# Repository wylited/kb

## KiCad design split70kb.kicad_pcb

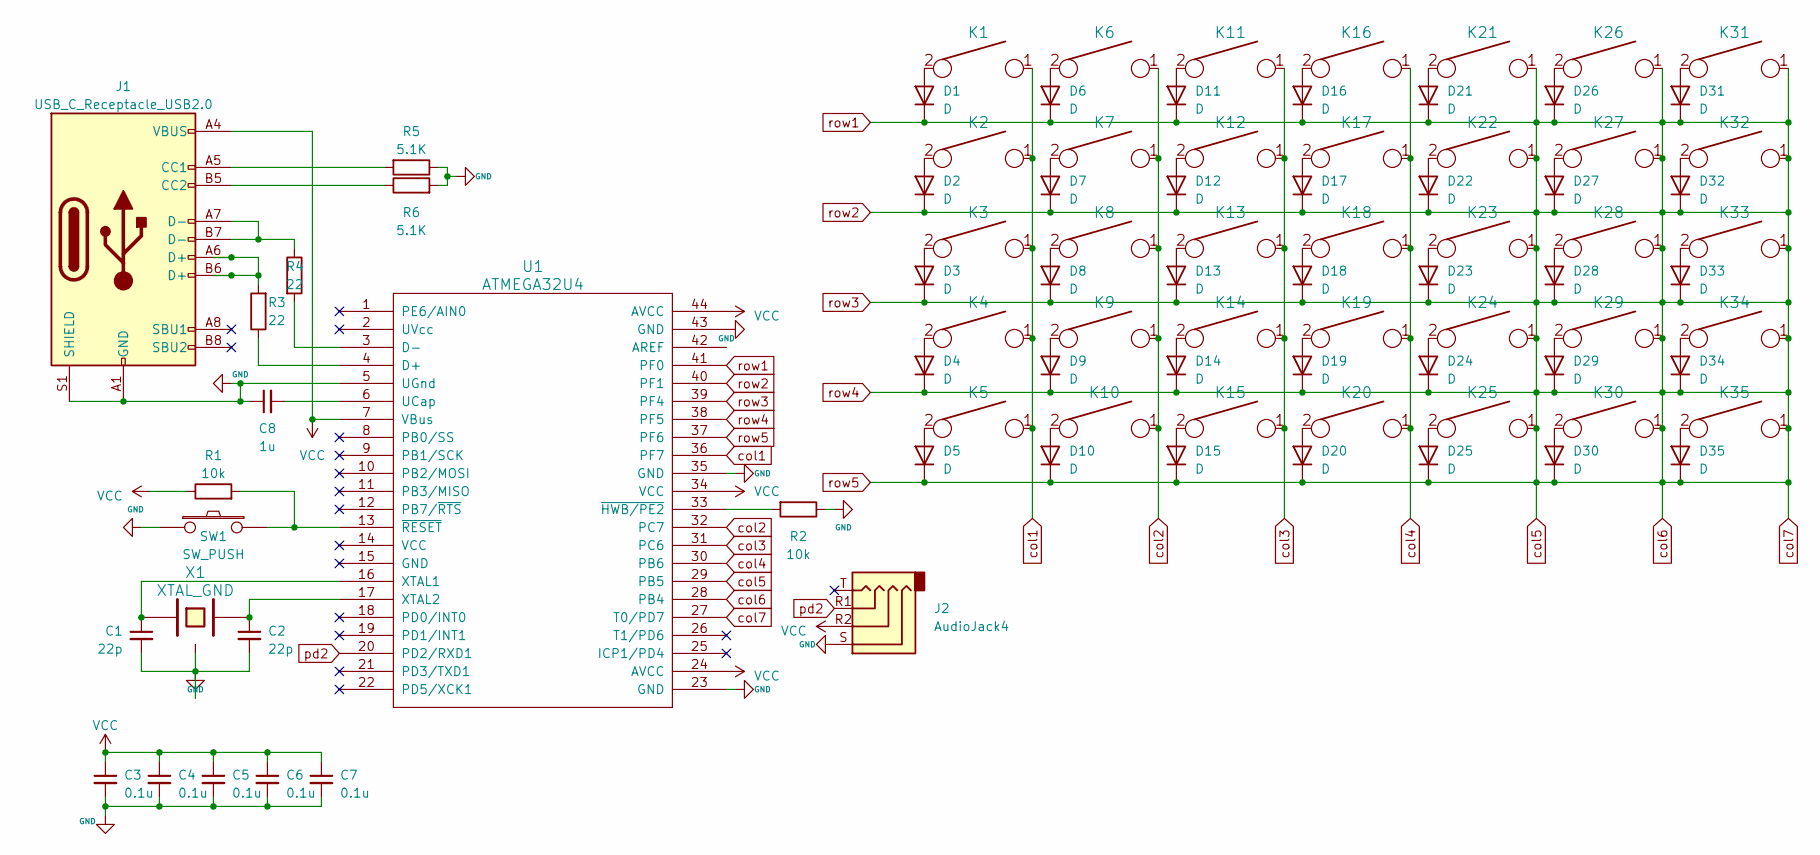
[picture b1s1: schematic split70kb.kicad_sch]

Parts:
C1, C2: 22p; C_0805_2012Metric
C3, C4, C5, C6, C7: 0.1u; C_0805_2012Metric
C8: 1u; C_0805_2012Metric
D1, D2, D3, D4, D5, D6, D7, D8, D9, D10, D11, D12, D13, D14, D15, D16, D17, D18, D19, D20, D21, D22, D23, D24, D25, D26, D27, D28, D29, D30, D31, D32, D33, D34, D35: D; D_SOD123_axial
J1: USB_C_Receptacle_USB2.0; USB_C_Receptacle_Molex_105450-0101
J2: AudioJack4; Jack_3.5mm_PJ320D_Horizontal
K1, K2, K3, K4, K5, K6, K7, K8, K9, K10, K11, K12, K13, K14, K15, K16, K17, K18, K19, K20, K21, K22, K23, K24, K25, K26, K27, K28, K29, K30, K31, K32, K33, K34, K35: KEYSW; Mx_Alps_100
R1, R2: 10k; R_0805_2012Metric
R3, R4: 22; R_0805_2012Metric
R5, R6: 5.1K; R_0805_2012Metric
SW1: SW_PUSH; SW_SPST_TL3342
U1: ATMEGA32U4; TQFP-44_10x10mm_P0.8mm
X1: XTAL_GND; Crystal_SMD_SeikoEpson_FA238-4Pin_3.2x2.5mm

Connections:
GND: C1.2, C2.2, C3.2, C4.2, C5.2, C6.2, C7.2, C8.1, J1.A1 (GND), J1.A12 (GND), J1.B1 (GND), J1.B12 (GND), J1.S1 (SHIELD), J2.S, R2.1, R5.1, R6.2, SW1.1, U1.5 (UGnd), U1.23 (GND), U1.35 (GND), U1.43 (GND), X1.3
unnamed: D1.2 (A), K1.2
unnamed: D2.2 (A), K2.2
unnamed: D3.2 (A), K3.2
unnamed: D4.2 (A), K4.2
unnamed: D5.2 (A), K5.2
unnamed: D6.2 (A), K6.2
unnamed: D7.2 (A), K7.2
unnamed: D8.2 (A), K8.2
unnamed: D9.2 (A), K9.2
unnamed: D10.2 (A), K10.2
unnamed: D11.2 (A), K11.2
unnamed: D12.2 (A), K12.2
unnamed: D13.2 (A), K13.2
unnamed: D14.2 (A), K14.2
unnamed: D15.2 (A), K15.2
unnamed: D16.2 (A), K16.2
unnamed: D17.2 (A), K17.2
unnamed: D18.2 (A), K18.2
unnamed: D19.2 (A), K19.2
unnamed: D20.2 (A), K20.2
unnamed: D21.2 (A), K21.2
unnamed: D22.2 (A), K22.2
unnamed: D23.2 (A), K23.2
unnamed: D24.2 (A), K24.2
unnamed: D25.2 (A), K25.2
unnamed: D26.2 (A), K26.2
unnamed: D27.2 (A), K27.2
unnamed: D28.2 (A), K28.2
unnamed: D29.2 (A), K29.2
unnamed: D30.2 (A), K30.2
unnamed: D31.2 (A), K31.2
unnamed: D32.2 (A), K32.2
unnamed: D33.2 (A), K33.2
unnamed: D34.2 (A), K34.2
unnamed: D35.2 (A), K35.2
unnamed: J1.A5 (CC1), R5.2
unnamed: J1.B5 (CC2), R6.1
unnamed: J1.A6 (D+), J1.B6 (D+), R3.2
unnamed: J1.A7 (D-), J1.B7 (D-), R4.1
unnamed: R3.1, U1.4 (D+)
unnamed: R4.2, U1.3 (D-)
unnamed: C8.2, U1.6 (UCap)
unnamed: C1.1, U1.16 (XTAL1), X1.1
unnamed: C2.1, U1.17 (XTAL2), X1.2
unnamed: R2.2, U1.33 (~HWB/PE2)
unnamed: R1.2, SW1.2, U1.13 (~RESET)
VCC: C3.1, C4.1, C5.1, C6.1, C7.1, J1.A4 (VBUS), J1.A9 (VBUS), J1.B4 (VBUS), J1.B9 (VBUS), J2.R2, R1.1, U1.7 (VBus), U1.24 (AVCC), U1.34 (VCC), U1.44 (AVCC)
col1: K1.1, K2.1, K3.1, K4.1, K5.1, U1.36 (PF7)
col2: K6.1, K7.1, K8.1, K9.1, K10.1, U1.32 (PC7)
col3: K11.1, K12.1, K13.1, K14.1, K15.1, U1.31 (PC6)
col4: K16.1, K17.1, K18.1, K19.1, K20.1, U1.30 (PB6)
col5: D1.1 (K), D2.1 (K), D3.1 (K), D4.1 (K), D5.1 (K), D6.1 (K), D7.1 (K), D8.1 (K), D9.1 (K), D10.1 (K), D11.1 (K), D12.1 (K), D13.1 (K), D14.1 (K), D15.1 (K), D16.1 (K), D17.1 (K), D18.1 (K), D19.1 (K), D20.1 (K), D21.1 (K), D22.1 (K), D23.1 (K), D24.1 (K), D25.1 (K), D26.1 (K), D27.1 (K), D28.1 (K), D29.1 (K), D30.1 (K), D31.1 (K), D32.1 (K), D33.1 (K), D34.1 (K), D35.1 (K), K21.1, K22.1, K23.1, K24.1, K25.1, K26.1, K27.1, K28.1, K29.1, K30.1, K31.1, K32.1, K33.1, K34.1, K35.1, U1.27 (T0/PD7), U1.28 (PB4), U1.29 (PB5), U1.37 (PF6), U1.38 (PF5), U1.39 (PF4), U1.40 (PF1), U1.41 (PF0)
pd2: J2.R1, U1.20 (PD2/RXD1)

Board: 2 copper layers, 88 parts (54 on the bottom side), 53 nets, no tracks yet.

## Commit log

2023-09-20 init
2023-09-22 finish schematic and pcb layout
2023-09-24 update for right side too in one board
2023-10-14 cleanup and shit
2023-12-17 reset
2023-12-17 initial schematic design
